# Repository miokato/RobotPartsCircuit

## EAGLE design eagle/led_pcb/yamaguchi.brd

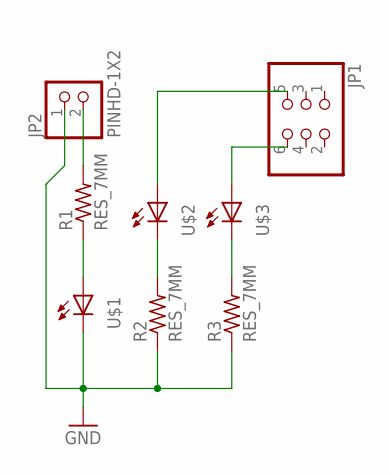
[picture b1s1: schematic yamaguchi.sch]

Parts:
JP1: PINHD-2X3; 2X03
JP2: PINHD-1X2; 1X02
R1, R2, R3: RES_7MM; 0204/7
U$1, U$2, U$3: LED1206; 1206

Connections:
GND: JP2.1, R2.1, R3.1, U$1.2 (C)
unnamed: JP2.2, R1.2
unnamed: R1.1, U$1.1 (A)
unnamed: R2.2, U$2.2 (C)
unnamed: R3.2, U$3.2 (C)
unnamed: JP1.6, U$3.1 (A)
unnamed: JP1.5, U$2.1 (A)

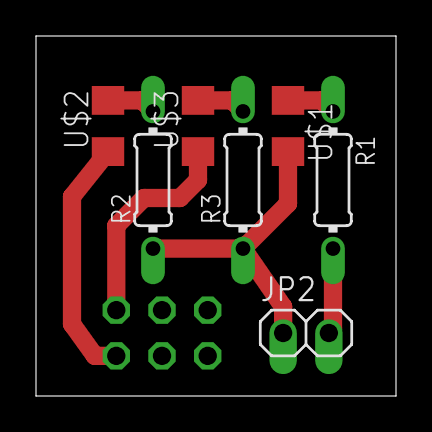
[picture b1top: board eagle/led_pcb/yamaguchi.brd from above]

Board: 2 copper layers, 20.0 x 20.0 mm, 8 parts (1 on the bottom side), 7 nets.

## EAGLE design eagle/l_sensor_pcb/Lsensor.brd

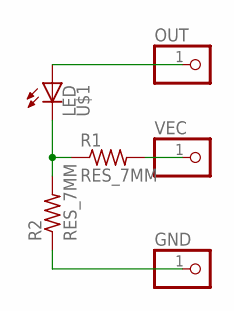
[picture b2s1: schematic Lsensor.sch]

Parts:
GND: PINHD-1X1; 1X01
OUT: PINHD-1X1; 1X01
R1, R2: RES_7MM; 0204/7
U$1: LED; 5MM
VEC: PINHD-1X1; 1X01

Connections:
unnamed: R1.2, VEC.1
unnamed: OUT.1, U$1.IN (A)
unnamed: R1.1, R2.2, U$1.OUT (C)
unnamed: GND.1, R2.1

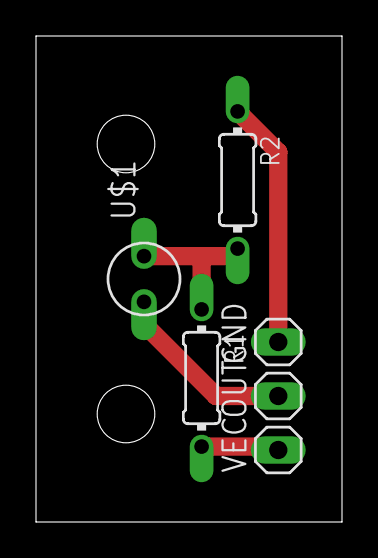
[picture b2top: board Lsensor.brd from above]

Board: 2 copper layers, 17.0 x 27.0 mm, 6 parts (0 on the bottom side), 4 nets.

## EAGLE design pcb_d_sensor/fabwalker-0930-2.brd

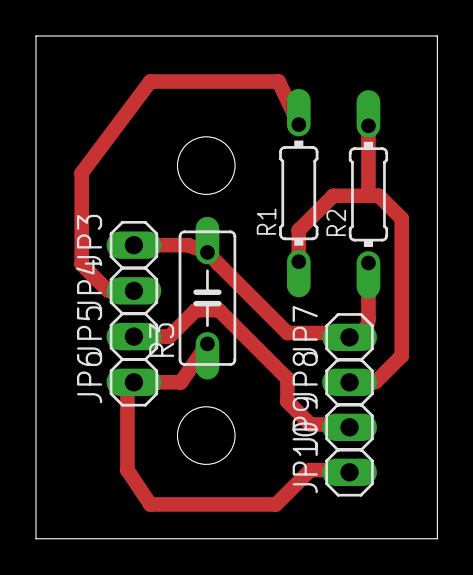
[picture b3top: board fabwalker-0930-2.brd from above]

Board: 2 copper layers, 22.3 x 27.9 mm, 11 parts (0 on the bottom side), 5 nets.

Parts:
JP3, JP4, JP5, JP6, JP7, JP8, JP9, JP10: 1X01
R1, R2: RES_7MM; 0204/7
R3: CAP_5MM; C050-030X075

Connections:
unnamed: JP3.1, JP7.1, R2.1, R3.2
unnamed: JP4.1, R1.2
unnamed: JP8.1, R1.1, R2.2
unnamed: JP6.1, JP10.1, R3.1
unnamed: JP5.1, JP9.1

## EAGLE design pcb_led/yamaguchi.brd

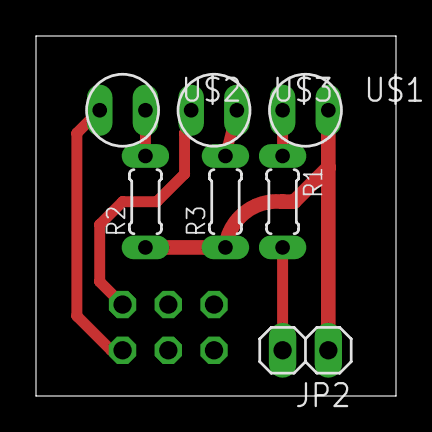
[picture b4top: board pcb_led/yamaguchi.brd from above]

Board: 2 copper layers, 20.0 x 20.0 mm, 8 parts (1 on the bottom side), 7 nets.

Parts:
JP1: 2X03
JP2: 1X02
R1, R2, R3: RES_5MM; 0204/5
U$1, U$2, U$3: LED; 5MM

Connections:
GND: JP2.1, R2.1, R3.1, U$1.OUT
unnamed: JP2.2, R1.2
unnamed: R1.1, U$1.IN
unnamed: R2.2, U$2.OUT
unnamed: R3.2, U$3.OUT
unnamed: JP1.6, U$3.IN
unnamed: JP1.5, U$2.IN

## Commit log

2016-09-30 first
2016-09-30 add one pin header
2016-10-03 add images
2016-10-03 add 3 pcbs
2016-10-03 add wiki
2016-10-03 fix images
2016-10-03 fix distance sensor pcb
2016-10-03 add light sensor pcb
2016-10-03 rename pcb files
2016-10-03 Home.md
2016-10-03 add sch and pcb file
2016-10-07 干渉を避けるためネジ穴の位置を修正
2016-10-07 穴の位置を修正してimageを作成
2016-10-07 資料の整理
2016-10-12 LED基板の回路図、切削ファイルを追加
2016-10-12 led基板の配線の修正
2016-10-12 LED基板の穴位置修正
2016-10-12 led基板の回路パターンを修正
